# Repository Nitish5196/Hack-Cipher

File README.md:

# Hack Cipher

## PCB Schematic 

## PCB 

## BOM

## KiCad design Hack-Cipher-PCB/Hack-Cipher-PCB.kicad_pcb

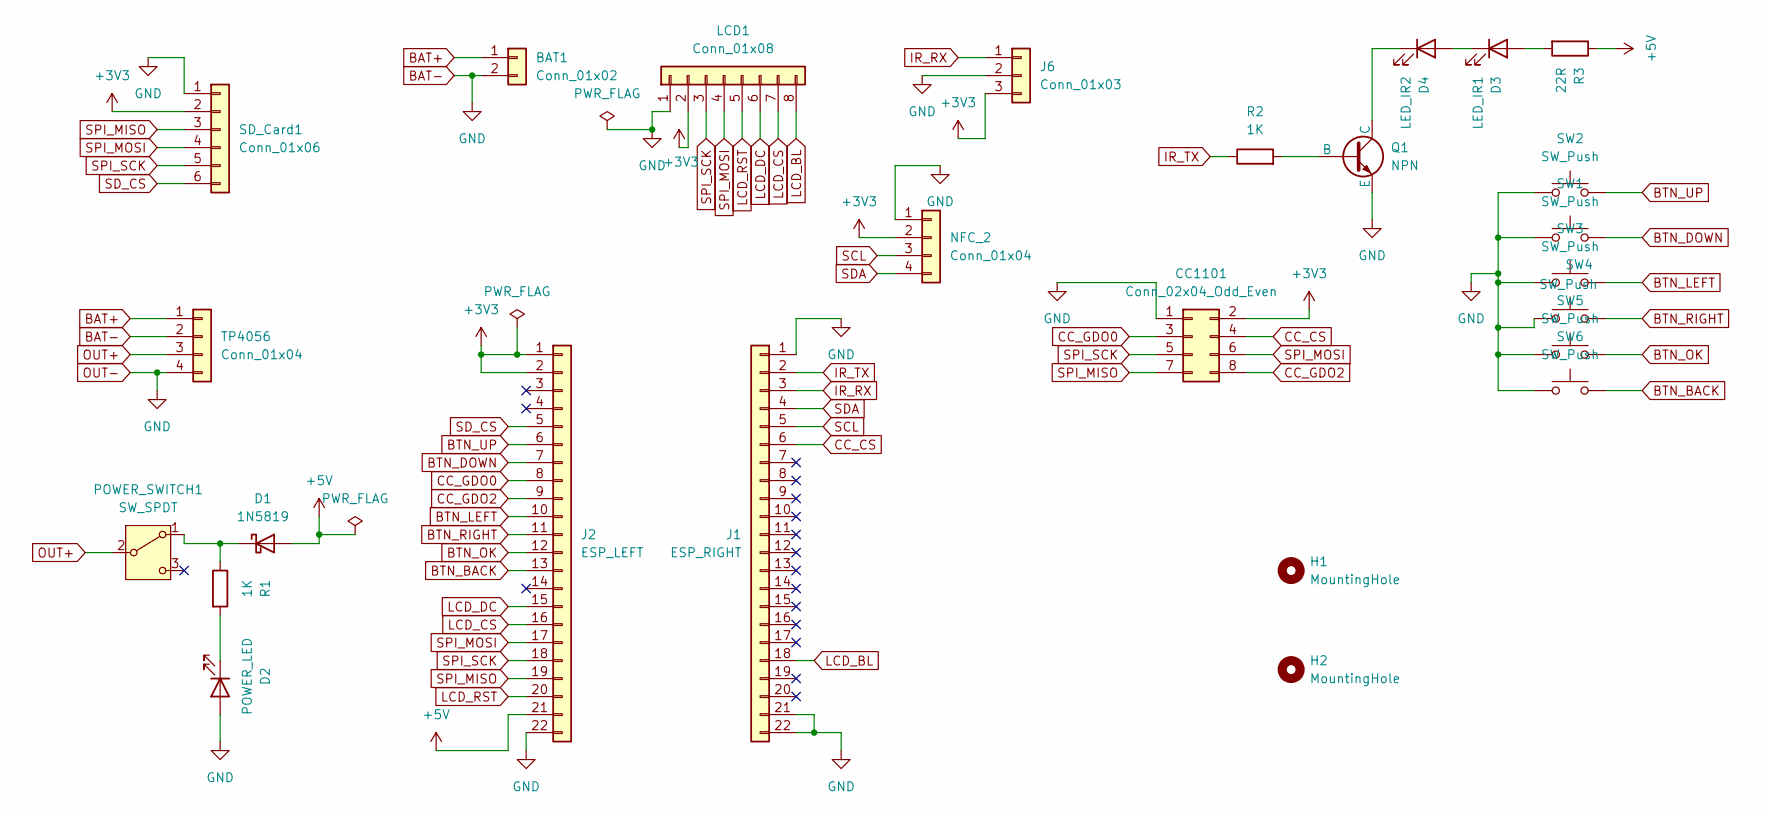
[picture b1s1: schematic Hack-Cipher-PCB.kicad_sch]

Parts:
BAT1: Conn_01x02; PinHeader_1x02_P2.54mm_Vertical
CC1101: Conn_02x04_Odd_Even; PinHeader_2x04_P2.54mm_Vertical
D1: 1N5819; D_DO-41_SOD81_P10.16mm_Horizontal
D2: POWER_LED; LED_D3.0mm
D3: LED_IR1; LED_D3.0mm
D4: LED_IR2; LED_D3.0mm
H1, H2: MountingHole; MountingHole_3.2mm_M3
J1: ESP_RIGHT; PinHeader_1x22_P2.54mm_Vertical
J2: ESP_LEFT; PinHeader_1x22_P2.54mm_Vertical
J6: Conn_01x03; PinHeader_1x03_P2.54mm_Vertical
LCD1: Conn_01x08; PinHeader_1x08_P2.54mm_Vertical
NFC_2: Conn_01x04; PinHeader_1x04_P2.54mm_Vertical
POWER_SWITCH1: SW_SPDT; SW_Slide_SPDT_Straight_CK_OS102011MS2Q
Q1: NPN; TO-92_HandSolder
R1, R2: 1K; R_Axial_DIN0204_L3.6mm_D1.6mm_P7.62mm_Horizontal
R3: 22R; R_Axial_DIN0204_L3.6mm_D1.6mm_P7.62mm_Horizontal
SD_Card1: Conn_01x06; PinHeader_1x06_P2.54mm_Vertical
SW1, SW2, SW3, SW4, SW5, SW6: SW_Push; SW_PUSH_6mm_H7.3mm
TP4056: Conn_01x04; PinHeader_1x04_P2.54mm_Vertical

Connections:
+3V3: CC1101.2, J2.1, J2.2, J6.3, LCD1.2, NFC_2.2, SD_Card1.2
+5V: D1.2 (A), J2.21, R3.1
BAT+: BAT1.1, TP4056.1
BAT-: BAT1.2, CC1101.1, D2.2 (A), J1.1, J1.21, J1.22, J2.22, J6.2, LCD1.1, NFC_2.1, Q1.3 (E), SD_Card1.1, SW1.1, SW2.1, SW3.1, SW4.1, SW5.1, SW6.1, TP4056.2, TP4056.4
BTN_BACK: J2.13, SW6.2
BTN_DOWN: J2.7, SW1.2
BTN_LEFT: J2.10, SW3.2
BTN_OK: J2.12, SW5.2
BTN_RIGHT: J2.11, SW4.2
BTN_UP: J2.6, SW2.2
CC_CS: CC1101.4, J1.6
CC_GDO0: CC1101.3, J2.8
CC_GDO2: CC1101.8, J2.9
IR_RX: J1.3, J6.1
IR_TX: J1.2, R2.1
LCD_BL: J1.18, LCD1.8
LCD_CS: J2.16, LCD1.7
LCD_DC: J2.15, LCD1.6
LCD_RST: J2.20, LCD1.5
unnamed: D1.1 (K), POWER_SWITCH1.1 (A), R1.1
unnamed: D2.1 (K), R1.2
unnamed: D3.2 (A), R3.2
unnamed: D3.1 (K), D4.2 (A)
unnamed: D4.1 (K), Q1.1 (C)
unnamed: Q1.2 (B), R2.2
OUT+: POWER_SWITCH1.2 (B), TP4056.3
SCL: J1.5, NFC_2.3
SDA: J1.4, NFC_2.4
SD_CS: J2.5, SD_Card1.6
SPI_MISO: CC1101.7, J2.19, SD_Card1.3
SPI_MOSI: CC1101.6, J2.17, LCD1.4, SD_Card1.4
SPI_SCK: CC1101.5, J2.18, LCD1.3, SD_Card1.5

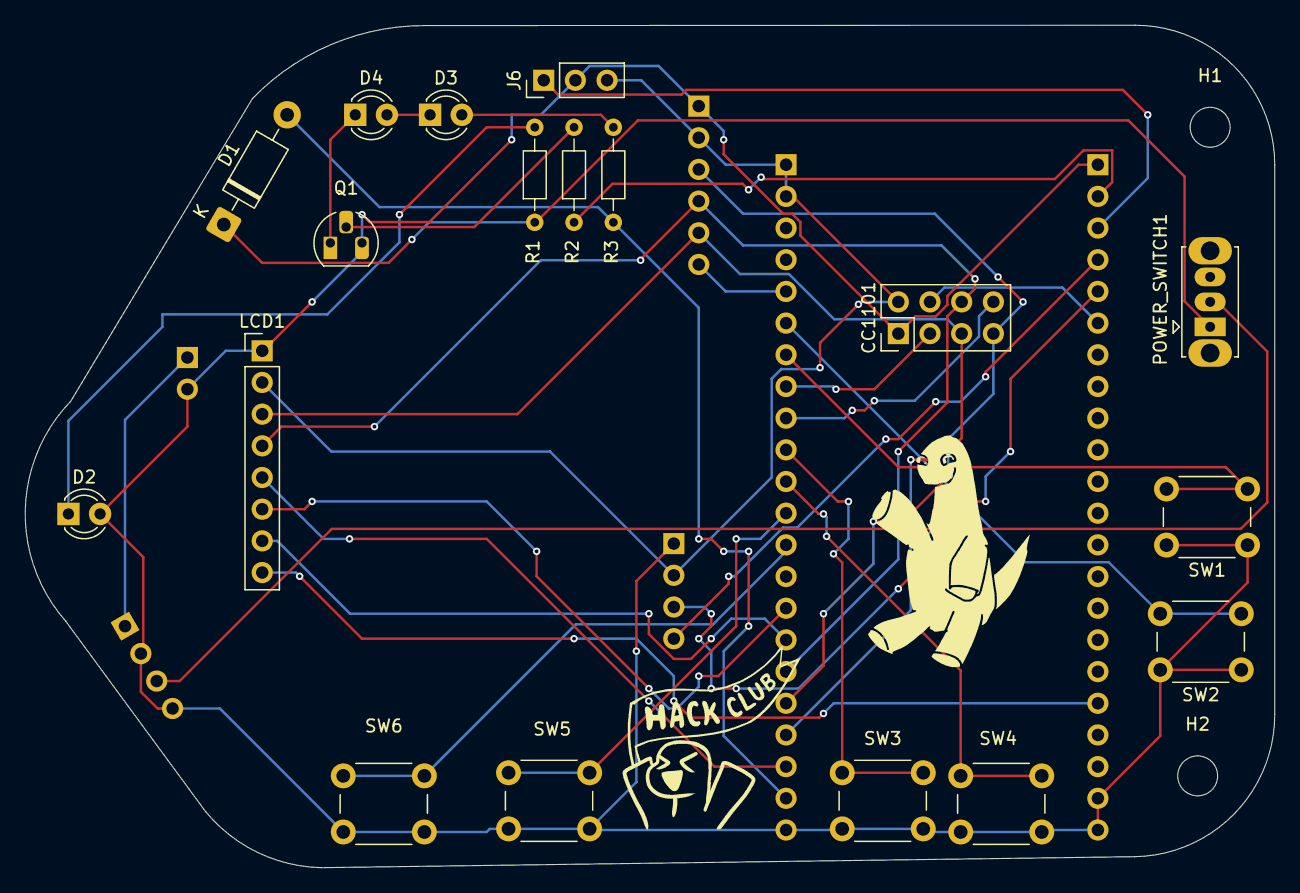
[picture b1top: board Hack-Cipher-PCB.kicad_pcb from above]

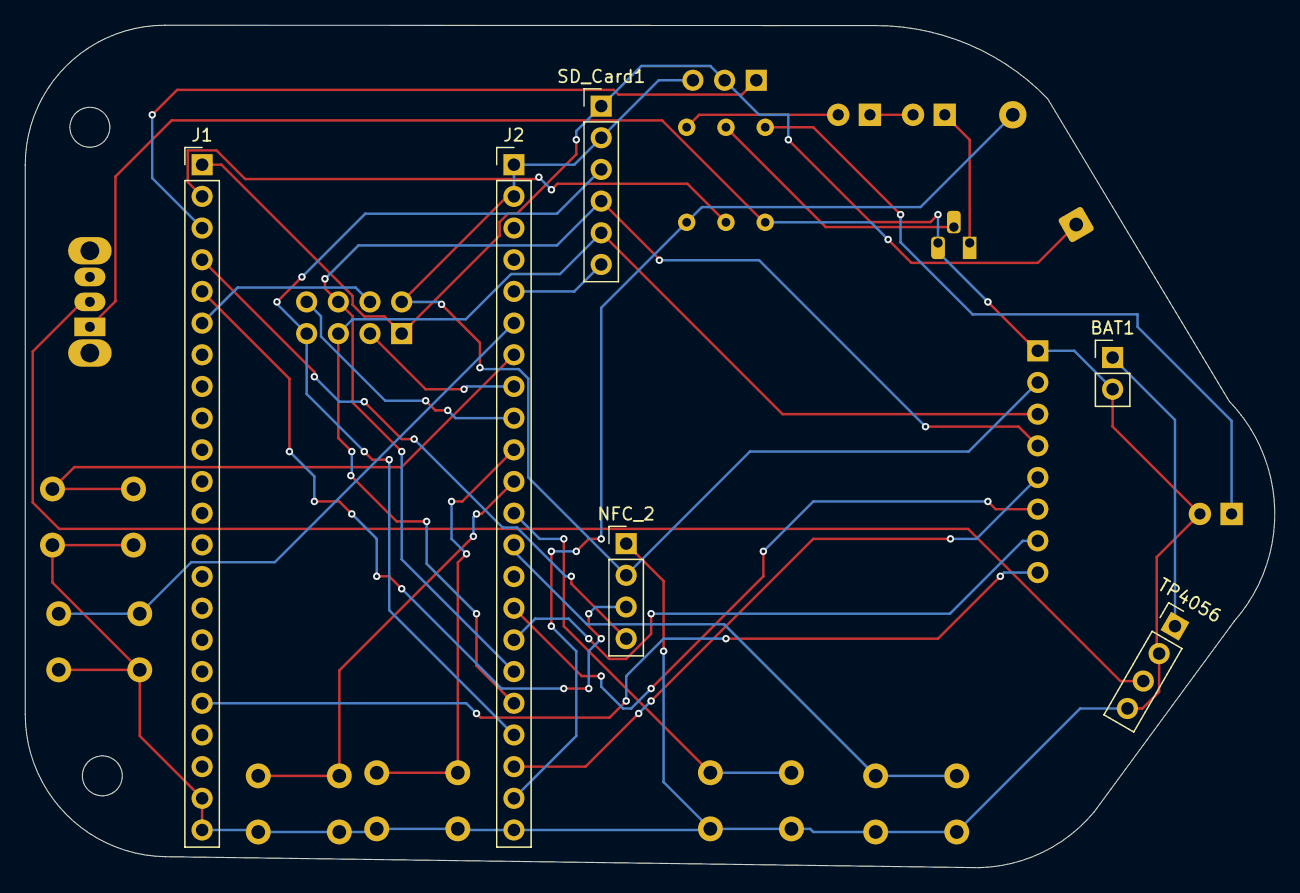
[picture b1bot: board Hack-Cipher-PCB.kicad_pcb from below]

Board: 2 copper layers, 100.2 x 67.5 mm, 26 parts (6 on the bottom side), 32 nets.

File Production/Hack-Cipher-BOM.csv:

"Id";"Designator";"Footprint";"Quantity";"Designation";"Supplier and ref";
1;"BAT1";"PinHeader_1x02_P2.54mm_Vertical";1;"Conn_01x02";;;
2;"CC1101";"PinHeader_2x04_P2.54mm_Vertical";1;"Conn_02x04_Odd_Even";;;
3;"D1";"D_DO-41_SOD81_P10.16mm_Horizontal";1;"1N5819";;;
4;"D2";"LED_D3.0mm";1;"POWER_LED";;;
5;"D3";"LED_D3.0mm";1;"LED_IR1";;;
6;"D4";"LED_D3.0mm";1;"LED_IR2";;;
7;"J1";"PinHeader_1x22_P2.54mm_Vertical";1;"ESP_RIGHT";;;
8;"J2";"PinHeader_1x22_P2.54mm_Vertical";1;"ESP_LEFT";;;
9;"J6";"PinHeader_1x03_P2.54mm_Vertical";1;"Conn_01x03";;;
10;"LCD1";"PinHeader_1x08_P2.54mm_Vertical";1;"Conn_01x08";;;
11;"NFC_2, TP4056";"PinHeader_1x04_P2.54mm_Vertical";2;"Conn_01x04";;;
12;"POWER_SWITCH1";"SW_Slide_SPDT_Straight_CK_OS102011MS2Q";1;"SW_SPDT";;;
13;"Q1";"TO-92_HandSolder";1;"NPN";;;
14;"R1, R2";"R_Axial_DIN0204_L3.6mm_D1.6mm_P7.62mm_Horizontal";2;"1K";;;
15;"R3";"R_Axial_DIN0204_L3.6mm_D1.6mm_P7.62mm_Horizontal";1;"22R";;;
16;"SD_Card1";"PinHeader_1x06_P2.54mm_Vertical";1;"Conn_01x06";;;
17;"SW1, SW2, SW3, SW4, SW5, SW6";"SW_PUSH_6mm_H7.3mm";6;"SW_Push";;;
